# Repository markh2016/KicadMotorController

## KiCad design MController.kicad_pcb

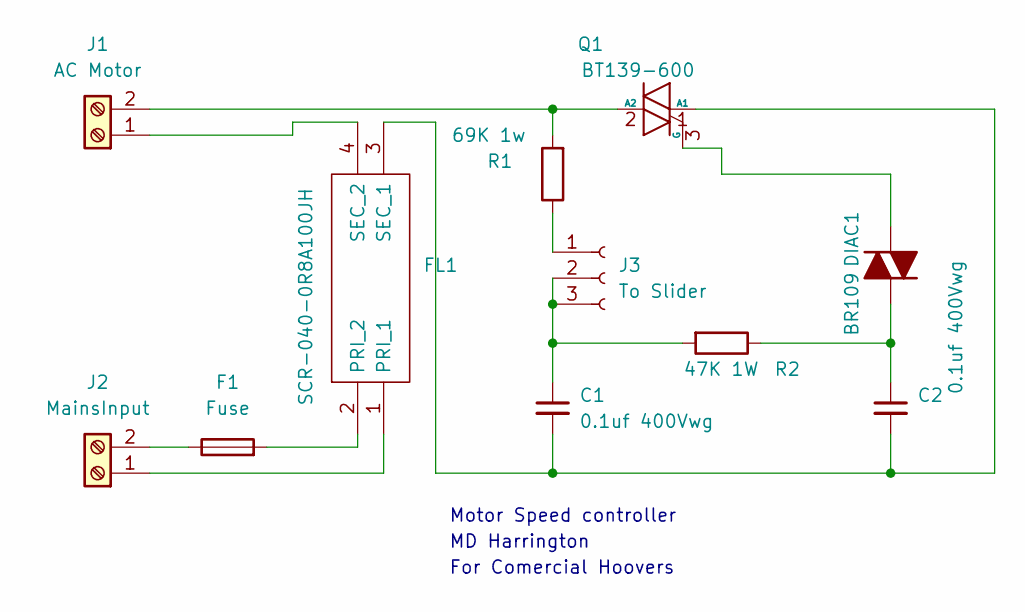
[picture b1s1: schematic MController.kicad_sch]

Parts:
C1, C2: 0.1uf 400Vwg; C_Axial_L12.0mm_D6.5mm_P20.00mm_Horizontal
DIAC1: BR109; D_DO-35_SOD27_P7.62mm_Horizontal
F1: Fuse; Fuseholder_Cylinder-5x20mm_Schurter_0031_8201_Horizontal_Op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
FL1: SCR-040-0R8A100JH; Choke_Schaffner_RN202-04-8.8x18.2mm; Manufacturer_Part_Number SCR-040-0R8A100JH; Mouser Part Number 80-SCR-040-0R8A100JH
J1: AC Motor; TerminalBlock_RND_205-00276_1x02_P5.00mm_Vertical
J2: MainsInput; TerminalBlock_RND_205-00276_1x02_P5.00mm_Vertical
J3: To Slider
Q1: BT139-600; TO-220-3_Vertical
R1: 69K 1w; R_Axial_DIN0207_L6.3mm_D2.5mm_P10.16mm_Horizontal
R2: 47K 1W; R_Axial_DIN0309_L9.0mm_D3.2mm_P15.24mm_Horizontal

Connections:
unnamed: C1.1, J3.2, J3.3, R2.2
unnamed: C2.1, DIAC1.1 (K), R2.1
unnamed: DIAC1.2 (A), Q1.3 (G)
unnamed: FL1.1 (PRI_1), J2.1
unnamed: F1.2, FL1.2 (PRI_2)
unnamed: FL1.4 (SEC_2), J1.1
unnamed: F1.1, J2.2
unnamed: J3.1, R1.1
unnamed: C1.2, C2.2, FL1.3 (SEC_1), Q1.1 (A1)
unnamed: J1.2, Q1.2 (A2), R1.2

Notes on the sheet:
For Comercial Hoovers
Motor Speed controller
MD Harrington

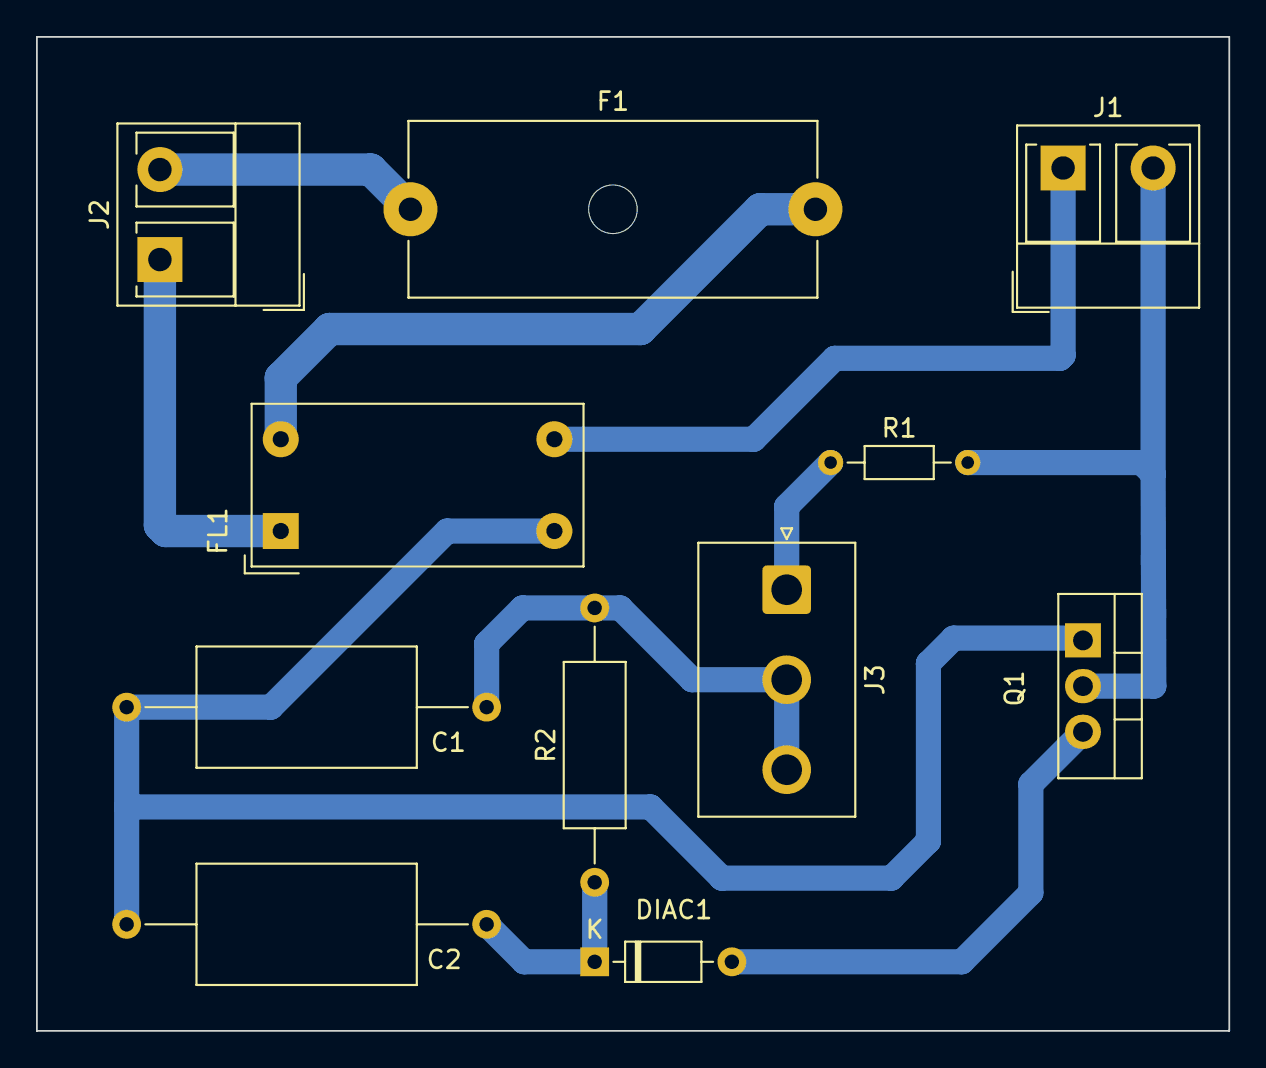
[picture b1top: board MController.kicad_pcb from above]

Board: 2 copper layers, 66.2 x 55.2 mm, 11 parts (0 on the bottom side), 10 nets.
